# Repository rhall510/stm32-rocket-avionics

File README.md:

# STM32-based rocket avionics unit and active tracking ground station

> **⚠️ NOTE: This project is currently in active development.**
> See the [project plan](docs/PROJECT_PLAN.md) for a detailed roadmap and the [development log](docs/DEVELOPMENT_LOG.md) for regular progress updates.

---

## Overview
This project aims to build a robust avionics unit for high power model rocketry. This system will also include a ground station that mechanically rotates a high gain antenna to actively track the rocket in real time during flight and receive critical telemetry data.

The system relies on sensor fusion for onboard state estimation and uses a hybrid RF tracking method combining position/movement telemetry received from the rocket and ranging with several ground nodes to accurately place the rocket.

## Key features
* **Dual-band telemetry:**
    * **2.4GHz (SX1280):** High bandwidth telemetry and ranging.
    * **868MHz (SX1262):** Command link.
* **Active ground tracking:** Motorized base with PID control tracks the rocket's position automatically using two independent data sources (on board avionics and ground ranging).
* **Live updating GUI:** See all relevant statistics and flight path updates in real time.
* **Advanced firmware:** Built on STM32 using FreeRTOS for concurrent sensor data acquisition, data logging, RF transmission, and parachute deployment.
* **Safety first:** Robust pre-flight check routine, redundant parachute deployment logic, and failsafe state management.

## System architecture
The project is divided into three main subsystems:

1.  **Avionics (Rocket):** Onboard PCB with flight sensors, NOR flash logging, and RF transceivers controlled by a STM32G474 microcontroller.
2.  **Ground station:** Network consisting of ranging nodes and a central controlling node with a motorised tracking base utilizing position telemetry to maintain a high gain link with the rocket.
3.  **Control center:** PC based GUI for live data visualization and controlling the ground station and avionics unit.

```mermaid
---
config:
  theme: neo-dark
  layout: dagre
---
flowchart TB
 subgraph Rocket["Avionics Unit"]
        MCU_R["MCU<br>STM32G474"]
        Sensors["Sensors<br>IMU, GPS, Baro"]
        NOR["NOR flash"]
        RKT_24["SX1280 2.4GHz"]
        RKT_868["SX1262 868MHz"]
        Parachute["Parachute<br>deployment"]
  end
 subgraph Air["Ground station (controller)"]
        GS_24["SX1280 2.4GHz"]
        GS_PDOA@{ label: "<span style=\"padding-left:\">SX1262 868MHz</span>" }
        MCU_G@{ label: "MCU<span style=\"padding-left:\"><br>STM32G474</span>" }
        Motors["Stepper/Servo<br>tracker base"]
        GUI["Qt GUI<br>Data display and<br> mission control"]
  end
 subgraph s1["Ground station (ranging nodes x2)"]
        n1["SX1280 2.4GHz<br>Ranging"]
        n2@{ label: "<span style=\"padding-left:\">SX1262 868MHz</span>" }
        n3@{ label: "MCU<span style=\"padding-left:\"><br>STM32G474</span>" }
  end
    Sensors -- SPI/I2C --> MCU_R
    MCU_R -- SPI --> RKT_868 & NOR
    MCU_R <-- SPI --> RKT_24
    MCU_R -- GPIO --> Parachute
    RKT_24 -. Telemetry .-> GS_24
    RKT_868 <-. Cmd .-> GS_PDOA
    GS_24 <-- SPI --> MCU_G
    GS_PDOA <-- SPI --> MCU_G
    MCU_G -- GPIO/PWM --> Motors
    MCU_G <-. USB .-> GUI
    GS_24 <-. Ranging .-> RKT_24
    n1 <-- SPI --> n3
    n2 <-- SPI --> n3
    n2 <-. Cmd .-> GS_PDOA

    GS_PDOA@{ shape: rect}
    MCU_G@{ shape: rect}
    n1@{ shape: rect}
    n2@{ shape: rect}
    n3@{ shape: rect}
```

## Repository structure
* `docs/`: Progress logs, planning documents, and testing data.
* `firmware/`: Source code for the avionics and ground station MCUs as well as other prototyping code.
* `hardware/`: KiCad schematics and PCB layouts.
* `mechanical/`: Model files for making various non-electrical parts of the project.
* `software/`: Source code for the control center GUI application.

## Current status
Goals from the [project plan](docs/PROJECT_PLAN.md) that are currently being worked on:

##### 2\. Avionics unit
* [ ] Implement and test parachute deployment logic.
* [ ] Final field tests of full avionics unit.

*For an up to date breakdown of progress, check the [development log](docs/DEVELOPMENT_LOG.md).*

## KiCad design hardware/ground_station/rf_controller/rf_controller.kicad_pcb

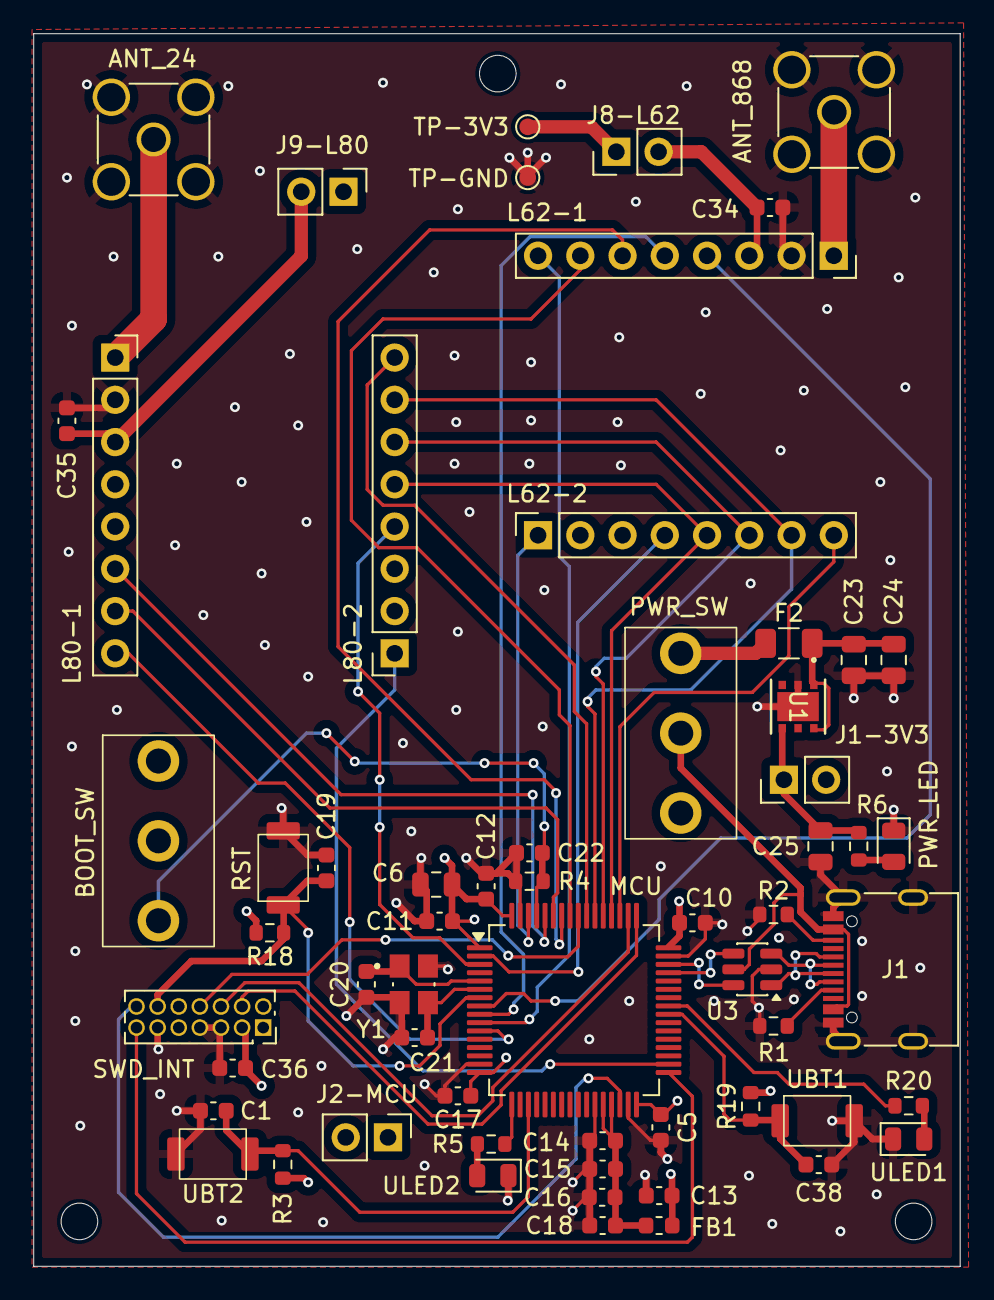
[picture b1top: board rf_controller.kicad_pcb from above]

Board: 4 copper layers, 55.7 x 74.1 mm, 63 parts (0 on the bottom side), 51 nets.

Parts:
ANT_24: 2.4GHz antenna; SMA_Amphenol_901-144_Vertical
ANT_868: 868MHz antenna; SMA_Amphenol_901-144_Vertical
BOOT_SW: SW_SPDT; SHOU HAN SS12D10G5
C1, C5, C10, C11, C12, C15, C17, C19, C22, C34, C35, C36, C38: 100nF; C_0603_1608Metric
C6: 4u7F; C_0805_2012Metric
C13, C16, C18: 1uF; C_0603_1608Metric
C14: 10nF; C_0603_1608Metric
C20, C21: 12pF; C_0603_1608Metric
C23: 22uF; C_0805_2012Metric
C24, C25: 1uF; C_0805_2012Metric
F2: 500mA; Fuse_1206_3216Metric
FB1: 120R; L_0603_1608Metric
H1, H2, H3: MountingHole; MountingHole_2.2mm_M2
J1: USB_C_Receptacle_USB2.0_16P; USB_C_Receptacle_G-Switch_GT-USB-7010ASV
J1-3V3, J2-MCU, J8-L62, J9-L80: Conn_01x02; PinHeader_1x02_P2.54mm_Vertical
L62-1: LAMBDA62; PinSocket_1x08_P2.54mm_Vertical
L62-2, L80-2: Conn_01x08_Socket; PinSocket_1x08_P2.54mm_Vertical
L80-1: LAMBDA80; PinSocket_1x08_P2.54mm_Vertical
MCU: STM32G474RET6; LQFP-64_10x10mm_P0.5mm
PWR_LED: PWR LED; LED_0805_2012Metric
PWR_SW: SW_SPDT; SHOU HAN SS12D10G5
R1, R2: 5k1R; R_0603_1608Metric
R3, R4, R18, R19: 10kR; R_0603_1608Metric
R5, R6, R20: 220R; R_0603_1608Metric
RST: SW_Push; hanxia HX 3x4x2-2P-1.6N TACTILE SWITCH
SWD_INT: SWD interface; PinSocket_2x07_P1.27mm_Vertical
TP-3V3: TestPoint; TestPoint_Pad_D1.0mm
TP-GND: TestPoint; TestPoint_Pad_D1.0mm
U1: LDL112PV33R; DFN_2PV33R_STM
U3: USBLC6-2SC6; SOT-23-6
UBT1, UBT2: SW_Push; hanxia HX 3x4x2-2P-1.6N TACTILE SWITCH
ULED1, ULED2: PWR LED; LED_0805_2012Metric
Y1: 16MHz; XTAL_ABM8G-16.000MHZ-4Y-T3

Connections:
+3V3: BOOT_SW.2 (B), C36.2, J1-3V3.2, J2-MCU.2, J8-L62.1, J9-L80.1, R3.1, R18.2, R19.2, SWD_INT.3, TP-3V3.1
+3V3A: C14.1, C15.1, C16.1, C18.1, FB1.1, MCU.28 (VREF+), MCU.29 (VDDA)
/BOOT0: BOOT_SW.3 (C), C22.1, MCU.61 (PB8), R4.1
/CONN_D+: J1.A6 (D+), J1.B6 (D+), U3.1 (I/O1)
/CONN_D-: J1.A7 (D-), J1.B7 (D-), U3.3 (I/O2)
/L62_ANT: ANT_868.1 (In), L62-1.1
/L62_BUSY: L62-1.6, MCU.58 (PB5)
/L62_CS: L62-2.8, MCU.51 (PA15)
/L62_DIO1: L62-1.7, MCU.57 (PB4)
/L62_DIO2: L62-1.8, MCU.10 (PC2)
/L62_DIO3: L62-2.1, MCU.62 (PB9)
/L62_RST: L62-2.4, MCU.2 (PC13)
/L62_RXSW: L62-1.4, MCU.8 (PC0)
/L62_TXSW: L62-1.5, MCU.9 (PC1)
/L62_VCC: C34.2, J8-L62.2, L62-1.3
/L80_ANT: ANT_24.1 (In), L80-1.1
/L80_BUSY: L80-1.6, MCU.60 (PB7)
/L80_CS: L80-2.8, MCU.55 (PD2)
/L80_DIO1: L80-1.7, MCU.59 (PB6)
/L80_DIO2: L80-1.8, MCU.11 (PC3)
/L80_DIO3: L80-2.1, MCU.34 (PB12)
/L80_RST: L80-2.4, MCU.3 (PC14)
/L80_VCC: C35.2, J9-L80.2, L80-1.3
/NRST: C19.1, MCU.7 (PG10), R18.1, RST.2, SWD_INT.12
/SPI3_MISO: L62-2.6, L80-2.6, MCU.53 (PC11)
/SPI3_MOSI: L62-2.7, L80-2.7, MCU.54 (PC12)
/SPI3_SCK: L62-2.5, L80-2.5, MCU.52 (PC10)
/SWCLK: MCU.50 (PA14), SWD_INT.6
/SWDIO: MCU.49 (PA13), SWD_INT.4
/SWO: MCU.56 (PB3), SWD_INT.8
/USB_D+: MCU.46 (PA12), U3.6 (I/O1)
/USB_D-: MCU.45 (PA11), U3.4 (I/O2)
/USB_VBUS: J1.A4 (VBUS), J1.A9 (VBUS), J1.B4 (VBUS), J1.B9 (VBUS), PWR_SW.2 (B), U3.5 (VBUS)
/VCC-MCU: C5.1, C6.1, C10.1, C11.1, C12.1, C13.1, C17.1, FB1.2, J2-MCU.1, MCU.1 (VBAT), MCU.16 (VDD), MCU.32 (VDD), MCU.48 (VDD), MCU.64 (VDD)
/VCP_RX: MCU.33 (PB11), SWD_INT.13
/VCP_TX: MCU.30 (PB10), SWD_INT.14
GND: ANT_24.2 (Ext), ANT_868.2 (Ext), C1.2, C5.2, C6.2, C10.2, C11.2, C12.2, C13.2, C14.2, C15.2, C16.2, C17.2, C18.2, C19.2, C20.2, C21.2, C22.2, C23.2, C24.2, C25.2, C34.1, C35.1, C36.1, C38.2, J1.A1 (GND), J1.A12 (GND), J1.B1 (GND), J1.B12 (GND), J1.S1 (SHIELD), L62-1.2, L80-1.2, MCU.15 (VSS), MCU.27 (VSSA), MCU.31 (VSS), MCU.47 (VSS), MCU.63 (VSS), PWR_LED.1 (K), R1.1, R2.1, R4.2, RST.1, SWD_INT.5, SWD_INT.7, SWD_INT.11, TP-GND.1, U1.2 (GND), U1.7 (EPAD), U3.2 (GND), UBT1.1, UBT2.1, ULED1.1 (K), ULED2.1 (K), Y1.2 (GND), Y1.4 (GND)
unnamed: C25.1, J1-3V3.1, R6.1, U1.4 (VOUT)
unnamed: J1.A5 (CC1), R1.2
unnamed: J1.B5 (CC2), R2.2
unnamed: MCU.17 (PA3), R5.2
unnamed: C1.1, MCU.19 (PA5), R3.2, UBT2.2
unnamed: C38.1, MCU.40 (PC8), R19.1, UBT1.2
unnamed: MCU.41 (PC9), R20.2
unnamed: C20.1, MCU.5 (PF0), Y1.1
unnamed: C21.1, MCU.6 (PF1), Y1.3
unnamed: PWR_LED.2 (A), R6.2
unnamed: F2.1, PWR_SW.1 (A)
unnamed: C23.1, C24.1, F2.2, U1.1 (EN), U1.6 (VIN)
unnamed: R20.1, ULED1.2 (A)
unnamed: R5.1, ULED2.2 (A)

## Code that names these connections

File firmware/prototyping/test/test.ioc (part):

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Mcu.Name=STM32G474R(B-C-E)Tx
Mcu.Package=LQFP64
Mcu.UserName=STM32G474RETx
PA13.Mode=Trace_Asynchronous_SW
PA13.Signal=SYS_JTMS-SWDIO
PA14.Mode=Trace_Asynchronous_SW
PA14.Signal=SYS_JTCK-SWCLK
PA3.Signal=GPIO_Output
PA5.Mode=Full_Duplex_Master
PA5.Signal=SPI1_SCK
PA6.Mode=Full_Duplex_Master
PA6.Signal=SPI1_MISO
PA7.Mode=Full_Duplex_Master
PA7.Signal=SPI1_MOSI
PA8.Mode=I2C
PA8.Signal=I2C2_SDA
PA9.Mode=I2C
PA9.Signal=I2C2_SCL
PB13.Mode=Full_Duplex_Master
PB13.Signal=SPI2_SCK
PB14.Mode=Full_Duplex_Master
PB14.Signal=SPI2_MISO
PB15.Mode=Full_Duplex_Master
PB15.Signal=SPI2_MOSI
PB3.Mode=Trace_Asynchronous_SW
PB3.Signal=SYS_JTDO-SWO
PC10.Mode=Full_Duplex_Master
PC10.Signal=SPI3_SCK
PC11.Mode=Full_Duplex_Master
PC11.Signal=SPI3_MISO
PC12.Mode=Full_Duplex_Master
PC12.Signal=SPI3_MOSI
PC4.Signal=GPXTI4
PC5.Signal=GPXTI5
PF0-OSC_IN.Mode=HSE-External-Oscillator
PF0-OSC_IN.Signal=RCC_OSC_IN
PF1-OSC_OUT.Mode=HSE-External-Oscillator
PF1-OSC_OUT.Signal=RCC_OSC_OUT
RCC.HSE_VALUE=16000000
RCC.SYSCLKFreq_VALUE=170000000
RCC.SYSCLKSource=RCC_SYSCLKSOURCE_PLLCLK
board=custom

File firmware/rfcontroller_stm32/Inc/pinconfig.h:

#ifndef PINCONFIG_H_
#define PINCONFIG_H_


// Debug peripherals
#define ULED1_PORT GPIOC
#define ULED1_PIN GPIO_PIN_9

#define ULED1_ON HAL_GPIO_WritePin(ULED1_PORT, ULED1_PIN, GPIO_PIN_SET);
#define ULED1_OFF HAL_GPIO_WritePin(ULED1_PORT, ULED1_PIN, GPIO_PIN_RESET);
#define ULED1_TOGGLE HAL_GPIO_TogglePin(ULED1_PORT, ULED1_PIN);

#define ULED2_PORT GPIOA
#define ULED2_PIN GPIO_PIN_3

#define ULED2_ON HAL_GPIO_WritePin(ULED2_PORT, ULED2_PIN, GPIO_PIN_SET);
#define ULED2_OFF HAL_GPIO_WritePin(ULED2_PORT, ULED2_PIN, GPIO_PIN_RESET);
#define ULED2_TOGGLE HAL_GPIO_TogglePin(ULED2_PORT, ULED2_PIN);

#define UBTN1_PORT GPIOC
#define UBTN1_PIN GPIO_PIN_8

#define UBTN1_READ HAL_GPIO_ReadPin(UBTN1_PORT, UBTN_PIN)

#define UBTN2_PORT GPIOA
#define UBTN2_PIN GPIO_PIN_5

#define UBTN2_READ HAL_GPIO_ReadPin(UBTN2_PORT, UBTN_PIN)


// LAMBDA62 pins
#define L62_CS_PORT GPIOA
#define L62_CS_PIN GPIO_PIN_15

#define L62_DIO1_PORT GPIOB
#define L62_DIO1_PIN GPIO_PIN_4

#define L62_DIO2_PORT GPIOC
#define L62_DIO2_PIN GPIO_PIN_2

#define L62_BUSY_PORT GPIOB
#define L62_BUSY_PIN GPIO_PIN_5

#define L62_RST_PORT GPIOC
#define L62_RST_PIN GPIO_PIN_13

#define L62_RXSW_PORT GPIOC
#define L62_RXSW_PIN GPIO_PIN_0

#define L62_TXSW_PORT GPIOC
#define L62_TXSW_PIN GPIO_PIN_1


// LAMBDA80 pins
#define L80_CS_PORT GPIOD
#define L80_CS_PIN GPIO_PIN_2

#define L80_DIO1_PORT GPIOB
#define L80_DIO1_PIN GPIO_PIN_6

#define L80_DIO2_PORT GPIOC
#define L80_DIO2_PIN GPIO_PIN_3

#define L80_BUSY_PORT GPIOB
#define L80_BUSY_PIN GPIO_PIN_7

#define L80_RST_PORT GPIOC
#define L80_RST_PIN GPIO_PIN_14










#endif /* PINCONFIG_H_ */

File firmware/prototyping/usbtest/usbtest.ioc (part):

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Mcu.Name=STM32G474R(B-C-E)Tx
Mcu.Package=LQFP64
Mcu.UserName=STM32G474RETx
PA11.Mode=Device
PA11.Signal=USB_DM
PA12.Mode=Device
PA12.Signal=USB_DP
PF0-OSC_IN.Mode=HSE-External-Oscillator
PF0-OSC_IN.Signal=RCC_OSC_IN
PF1-OSC_OUT.Mode=HSE-External-Oscillator
PF1-OSC_OUT.Signal=RCC_OSC_OUT
RCC.HSE_VALUE=16000000
RCC.SYSCLKFreq_VALUE=144000000
RCC.SYSCLKSource=RCC_SYSCLKSOURCE_PLLCLK
board=custom

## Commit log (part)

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2026-01-26 Updated development log with all progress so far
2026-01-28 Began making avionics development PCB. Started with the power circuitry which uses a TPS563201 buck converter to provide a stable 3.3V DC source.
2026-01-28 Update devlog
2026-01-28 Fixed missing trace on avionics dev pcb
2026-02-01 Fixed packet sequence miscouting error and finalised avionics component selections
2026-02-02 Started designing stm32g474ret6 section of the PCB schematic. Done power supply, external crystal oscillator, and BOOT0 and NRST pins so far
2026-02-04 Updated PCB schematic with sensors and storage devices
2026-02-07 Avionics dev board schematic done
2026-02-08 Updated component selections and footprints assigned
2026-02-09 First revision of avionics dev board PCB - needs routing fixes
2026-02-10 Avionics dev PCB revision 2 - improved stackup and routing
2026-02-10 Cleanup and refinements to avionics dev board PCB
2026-02-11 Improved shielding of GPS RF trace and added 0 ohm resistors to switch SWD RX and TX if necessary
2026-02-12 Added pull up/down resistors to some pins according to datasheet recommendations
2026-02-28 Bare metal startup code for STM32G431KB
2026-03-10 Log file update
2026-03-15 Avionics dev board V2
2026-03-15 Added power isolation jumper to regulator output and improved fuse placement
2026-04-01 Devlog update
2026-04-09 Startup code and basic LSM6DSR FIFO reading firmware
2026-04-09 Improved LSM6DSR FIFO reading and small calibration + integration test
2026-04-10 Implemented basic FIFO data retreival from ADXL375 accelerometer
2026-04-15 Implemented basic initialisation and FIFO data retreival from BMP581
2026-04-18 Implemented basic initialisation and data retreival from MMC5983MA
2026-04-19 Initialisation code for W25Q flash. Updated project plan and devlog
2026-04-22 Implemented metadata read/write and page programming functions to the W25Q driver
2026-04-24 Finished first pass of all functions in the W25Q driver
2026-04-24 B Finished first pass of all functions in the W25Q driver
    Fixes:
    - Updated all functions to use the 5 global metadata variables instead of passing around a long list of pointers
    - Fixed pointer math in data reading section of W25Q_ReadMetadata() to use the safe address getting function
    - Fixed potential issue in W25Q_ReadMetadata() where the data end address could be one less than the data start address if no data is present (essentially marking every part of memory as filled with 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
    - Fixed the starting search address to 0x0 in W25Q_GetSafeMetadataAddress()
    - Removed default argument from W25Q_WriteMetadata() - (this is a C++ feature, not C!)
2026-04-24 Fixed a few minor syntax errors in W25Q driver
2026-04-24 Lots of bugfixing and further progress on W25Q driver
    Fixes:
    - Fixed potential buffer overflow in read volume functions due to read
    length not being taken into account when transferring data into the
    buffer
    - Fixed an infinite loop in W25Q_GetSafeContiguousReadAddressWithOffset
    caused by checking the Offset variable rather than OffsetLeft
2026-04-25 Added a small function to test the bad block scanning logic. It seems to work perfectly and detects no bad blocks!
2026-04-25 Added new testing functions for W25Q - Added Test_W25Q_Initialisation which tests initialisation and reading of existing data on the chip - Added Test_W25Q_Logging which tests erasure of previous fli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
    All of these tests pass perfectly. Test logs in docs/dev_board_planning.
2026-04-25 Update readme and project plan
2026-04-28 Started making some basic functions for the LAMBDA62 driver
2026-04-29 LAMBDA62 driver update - Added read and write register functions - Added a workaround to the initialisation function from section 15.2 of the SX1262 datasheet to improve handling of antenna mismatches
2026-04-29 Finished basic LAMBDA62 driver. Started porting over everything to make LAMBDA80 driver
2026-05-01 Finished all main functions of the LAMBDA80 driver
2026-05-01 Expanded data logging functionality - Moved NMEA parsing functions to the m10s driver to clean up the main file - Added 'AppendLogPacket' functions to each sensor driver to cleanly generate byte arra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
2026-05-02 Testing serial communication between NUCLEO G431KB board and a host PC - Made a quick project using cubeMX to initialise a NUCLEO G431KB board and send a test string over USART2 to a host PC via a vi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
2026-05-03 Basic data download link finished - no error correction yet - Made a few small python scripts for receiving data from the avionics unit - Fixed invalid 0 value for preamble length exponent in SetPack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
2026-05-04 Data decoding tests - Wrote a python script to decode the raw binary packets received from the avionics unit into useable data - Added responsiveness checks to all sensor initialisation functions
    There is currently an issue where the LSM6DSR does not seem to be
    logging packets. Investigation is under way.
2026-05-05 Data recording and transmission bugfixing - Fixed LAMBDA62 DIO1 initialisation masking LSM6DSR EXTI interrupt line - Fixed wrong type encoding for MAX-M10S data packets
2026-05-06 - Added functions to each sensor driver to pause data acquisition when not needed - Added a function to automatically structure and send UBX messages to the MAX-M10S module
2026-05-12 Command link plan and start of RF controller board
2026-05-13 PCB layout for RF controller And additional updates to schematic: - Added ESD protection to USB data lines - Fixed wrong placement of capacitors around LDO voltage regulator - Added extra user LED an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
2026-05-15 Finalised RF controller PCB layout
2026-05-15 Added GFSK initialisation and packet configuration functions to LAMBDA62 driver
2026-06-07 Set up RF controller project with FreeRTOS and TinyUSB integrations
2026-06-08 Added full initialisation code for RF controller and ported over LAMBDA drivers
2026-06-09 Attempting to fix USB descriptor bug
2026-06-10 USB descriptor bug fixed
2026-06-12 Implemented some basic USB tasks for RF controller and made a simple bidirectional serial terminal application
2026-06-13 Implemented a robust and extensible USB command handling framework for the RF controller. Also updated the serial terminal to be able to send and receive data as hex instead of ascii
2026-06-14 Started integrating network packet handling for RF controller
2026-06-15 Added a microsecond timer and started converting radio driver functions to RTOS friendly versions
2026-06-16 Started implementing FreeRTOS for the main avionics board
2026-06-17 Started implementing network discovery protocol
2026-06-18 Tying to fix radio communication bugs
2026-06-19 Radio discovery protocol working
2026-06-20 Added a basic packet testing command (only 868MHz currently)
2026-06-21 Improved the packet testing mode to switch continuously between 868MHz and 2.4GHz
2026-06-22 Attempting to fix intermittent radio module unresponsiveness
2026-06-23 Fixed LAMBDA80 module intermittent Tx timeout and lockup during test packet response
2026-06-25 Added USB transmission of packet test data and updated the serial terminal to parse and plot the data live
2026-06-26 Some bugfixing and refactoring of the RF controller and avionics packet handling code

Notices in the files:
README.md:
License: MIT
